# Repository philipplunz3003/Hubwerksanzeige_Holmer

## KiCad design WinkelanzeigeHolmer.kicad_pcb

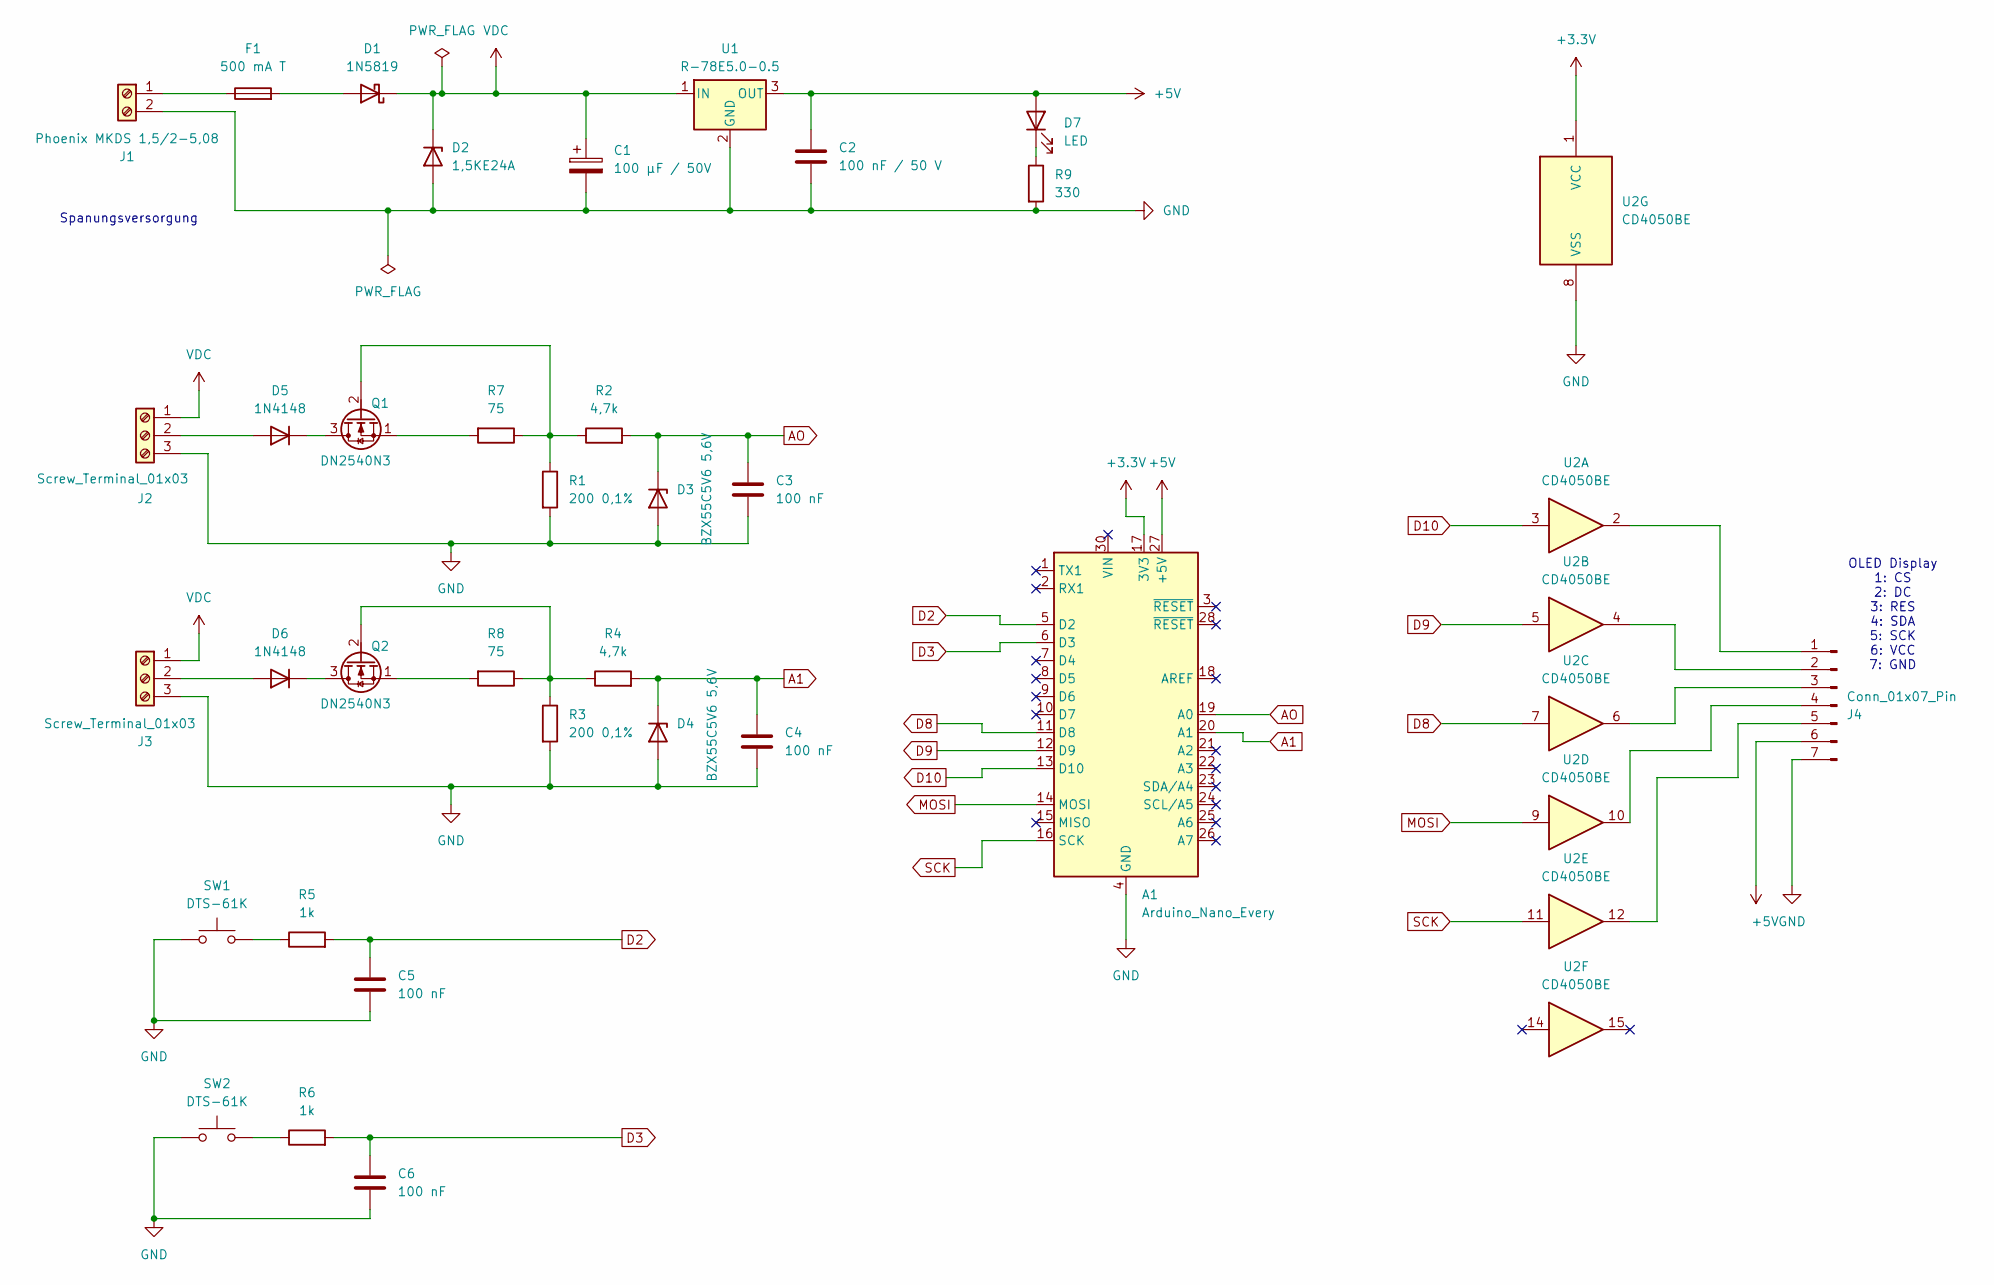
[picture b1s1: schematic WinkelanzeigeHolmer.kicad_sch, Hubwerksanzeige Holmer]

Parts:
A1: Arduino_Nano_Every; Arduino_Nano
C1: 100 µF / 50V; CP_Radial_D6.3mm_P2.50mm
C2: 100 nF / 50 V; C_Disc_D5.0mm_W2.5mm_P5.00mm
C3, C4, C5, C6: 100 nF; C_Disc_D5.0mm_W2.5mm_P5.00mm
D1: 1N5819; D_DO-41_SOD81_P10.16mm_Horizontal
D2: 1,5KE24A; D_DO-201AD_P12.70mm_Horizontal
D3, D4: BZX55C5V6 5,6V; D_DO-35_SOD27_P7.62mm_Horizontal
D5, D6: 1N4148; D_DO-35_SOD27_P7.62mm_Horizontal
D7: LED; LED_D5.0mm
F1: 500 mA T; Fuseholder_Cylinder-5x20mm_Schurter_0031_8201_Horizontal_Op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
J1: Phoenix MKDS 1,5/2-5,08; TerminalBlock_Phoenix_MKDS-1,5-2-5.08_1x02_P5.08mm_Horizont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
J2, J3: Screw_Terminal_01x03; TerminalBlock_Phoenix_MKDS-1,5-3-5.08_1x03_P5.08mm_Horizont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
J4: Conn_01x07_Pin; PinHeader_1x07_P2.54mm_Vertical
Q1, Q2: DN2540N3; TO-92L_HandSolder
R1, R3: 200 0,1%; R_Axial_DIN0207_L6.3mm_D2.5mm_P10.16mm_Horizontal
R2, R4: 4,7k; R_Axial_DIN0207_L6.3mm_D2.5mm_P10.16mm_Horizontal
R5, R6: 1k; R_Axial_DIN0207_L6.3mm_D2.5mm_P10.16mm_Horizontal
R7, R8: 75; R_Axial_DIN0207_L6.3mm_D2.5mm_P10.16mm_Horizontal
R9: 330; R_Axial_DIN0207_L6.3mm_D2.5mm_P10.16mm_Horizontal
SW1, SW2: DTS-61K; SW_PUSH_6mm_H4.3mm
U1: R-78E5.0-0.5; Converter_DCDC_RECOM_R-78E-0.5_THT
U2: CD4050BE; CERDIP-16_W7.62mm_SideBrazed_LongPads_Socket

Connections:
+3.3V: A1.17 (3V3), U2.1 (VCC)
+5V: A1.27 (+5V), C2.1, D7.2 (A), J4.6, U1.3 (OUT)
A1: A1.20 (A1), C4.1, D4.1 (K), R4.2
AO: A1.19 (A0), C3.1, D3.1 (K), R2.2
D2: A1.5 (D2), C5.1, R5.2
D3: A1.6 (D3), C6.1, R6.2
D8: A1.11 (D8), U2.7
D9: A1.12 (D9), U2.5
D10: A1.13 (D10), U2.3
GND: A1.4 (GND), A1.29 (GND), C1.2, C2.2, C3.2, C4.2, C5.2, C6.2, D2.2 (A), D3.2 (A), D4.2 (A), J1.2, J2.3, J3.3, J4.7, R1.2, R3.2, R9.2, SW1.1, SW2.1, U1.2 (GND), U2.8 (VSS)
MOSI: A1.14 (MOSI), U2.9
unnamed: D1.2 (A), F1.2
unnamed: D5.2 (A), J2.2
unnamed: D5.1 (K), Q1.3 (D)
unnamed: D6.2 (A), J3.2
unnamed: D6.1 (K), Q2.3 (D)
unnamed: D7.1 (K), R9.1
unnamed: F1.1, J1.1
unnamed: J4.1, U2.2
unnamed: J4.2, U2.4
unnamed: J4.3, U2.6
unnamed: J4.4, U2.10
unnamed: J4.5, U2.12
unnamed: Q1.2 (G), R1.1, R2.1, R7.1
unnamed: Q1.1 (S), R7.2
unnamed: Q2.2 (G), R3.1, R4.1, R8.1
unnamed: Q2.1 (S), R8.2
unnamed: R5.1, SW1.2
unnamed: R6.1, SW2.2
SCK: A1.16 (SCK), U2.11
VDC: C1.1, D1.1 (K), D2.1 (K), J2.1, J3.1, U1.1 (IN)

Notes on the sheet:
Spanungsversorgung
OLED Display 1: CS 2: DC 3: RES 4: SDA 5: SCK 6: VCC 7: GND

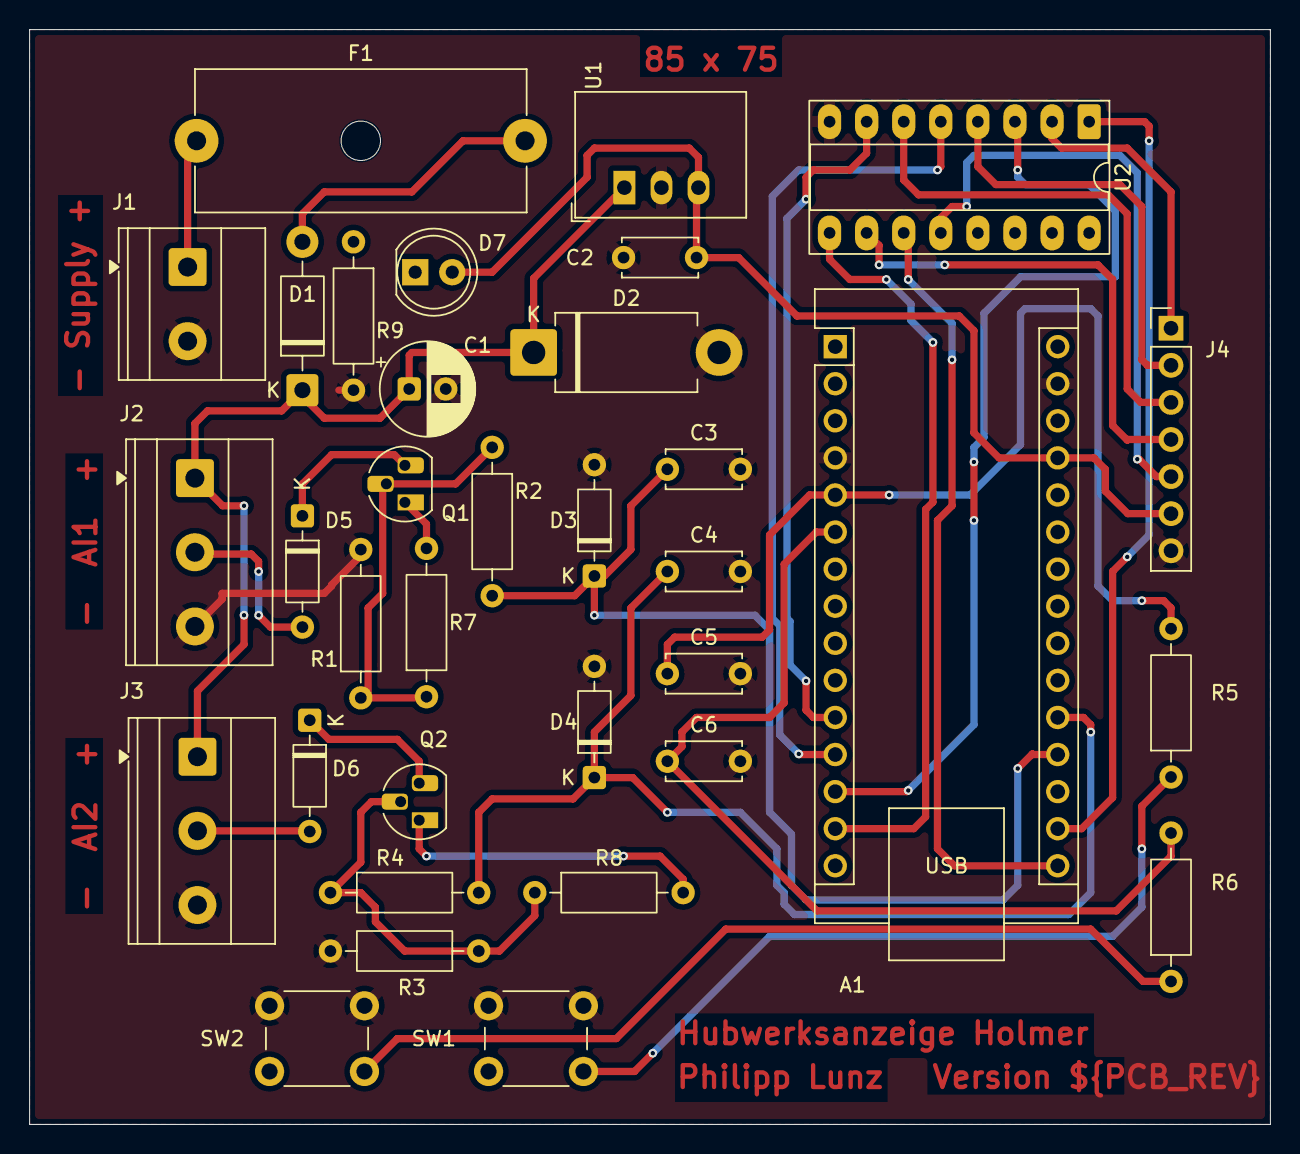
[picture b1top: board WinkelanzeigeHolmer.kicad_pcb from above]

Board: 2 copper layers, 85.0 x 75.0 mm, 34 parts (0 on the bottom side), 31 nets.
